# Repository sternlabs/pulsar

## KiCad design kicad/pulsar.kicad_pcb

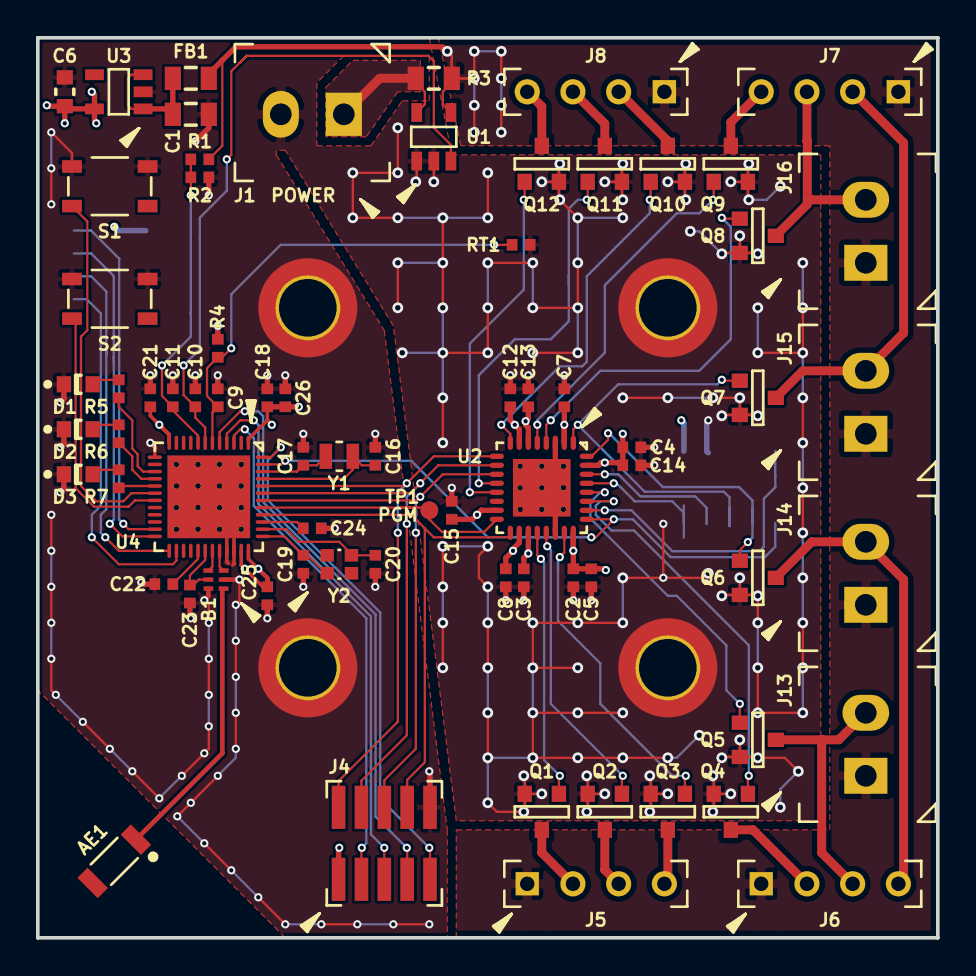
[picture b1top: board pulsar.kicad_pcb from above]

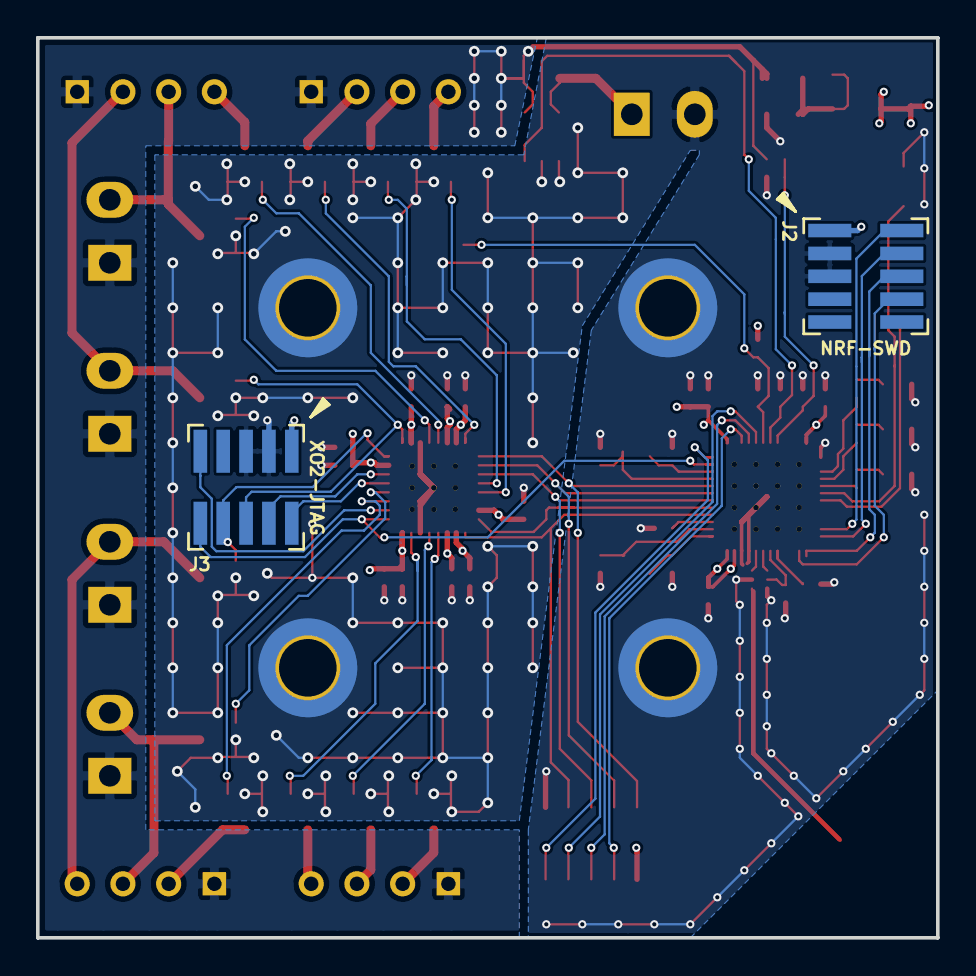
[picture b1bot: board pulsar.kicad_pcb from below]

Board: 4 copper layers, 50.0 x 50.0 mm, 77 parts (2 on the bottom side), 67 nets.

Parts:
AE1: ANT; ANT3216
B1: nRF-BALUN; BALUN-2450BM14E0003
C1: 10u; SMD-2012
C2, C3, C4, C7, C8, C12, C13, C14, C18, C21, C24: 100n; SMD-1005
C5, C15, C26: 1u; SMD-1005
C6: 4.7u; SMD-1608
C9, C10, C11, C22: 47n; SMD-1005
C16, C17: 20p; SMD-1005
C19, C20: 7p; SMD-1005
C23, C25: 2.2n; SMD-1005
D1, D2, D3: LED; SMD-1608-LED
FB1: FERRITE; SMD-2012
J1: POWER; TERM-2-3.5-PTH
J2: NRF-SWD; CONN-2x5-1.27-SMT
J3: XO2-JTAG; CONN-2x5-1.27-SMT
J4: CONN-2x5; CONN-2x5-1.27-SMT
J5, J6, J7, J8: CONN-4; CONN-4-2.54-0.8-PTH
J13, J14, J15, J16: CONN-2; TERM-2-3.5-PTH
MH1, MH2, MH3, MH4: MOUNTHOLE; HOLE-M3-COND
Q1, Q2, Q3, Q4, Q5, Q6, Q7, Q8, Q9, Q10, Q11, Q12: NMOS; SOT-23-FET
R1: 124k; SMD-1005
R2: 10k; SMD-1005
R3: 5m; SMD-2012
R4: 22k; SMD-1005
R5, R6, R7: 1k; SMD-1005
RT1: 47k; SMD-1005
S1, S2: TACTILE-4; TACT-4632
TP1: PGM; TESTPOINT-1.0
U1: TS1102-50; SOT-23-5
U2: XO2-256; xo2-256-qfn32
U3: MIC5205; SOT-23-5
U4: nrf51822; nrf51822-qfn48
Y1: 32kHz; OSC2012
Y2: 32MHz; OSC2016

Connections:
+3V3: C2.1, C3.1, C4.1, C5.1, C6.1, C7.1, C8.1, C12.1, C13.1, C14.1, C15.1, C18.1, C21.1, C25.1, C26.1, J2.1, J3.1, J4.1, R4.1, U2.2, U2.6, U2.7, U2.15, U2.18, U2.19, U2.24, U2.31, U3.5, U4.1, U4.12, U4.35, U4.36
/ANT: AE1.ANT, B1.1
/AUX1: J4.3, U4.3
/AUX2: J4.5, U4.4
/AUX3: J4.7, U4.5
/AUX4: J4.9, U4.48
/BUTTON1: S1.2, U4.18
/BUTTON2: S2.2, U4.19
/IIN_SENSE: C10.1, U1.3, U4.7
/LED1: R5.1, U4.15
/LED2: R6.1, U4.16
/LED3: R7.1, U4.17
/NRF_SWDCLK: J2.4, U4.24
/NRF_SWDIO/~RESET: J2.2, U4.23
/RAW_VIN: J1.1, R3.1, U1.5
/RX: J2.8, U4.26
/SPI_CLK: J4.2, U2.9, U4.44
/SPI_CS: J4.6, U2.11, U4.42
/SPI_CS_PGM: TP1.TP, U2.16, U4.41
/SPI_MISO: J4.4, U2.10, U4.43
/SPI_MOSI: J4.8, U2.17, U4.40
/TEMP_SENSE: C9.1, R4.2, RT1.1, U4.6
/TX: J2.6, U4.25
/VIN_SENSE: C11.1, R1.2, R2.1, U4.8
/XO2_JTAG_TCK: J3.4, U2.30
/XO2_JTAG_TMS: J3.2, U2.29
/rgb1/CH1: Q1.G, U2.20
/rgb1/CH1_OUT: J5.2, Q1.D
/rgb1/CH2: Q2.G, U2.21
/rgb1/CH2_OUT: J5.3, Q2.D
/rgb1/CH3: Q3.G, U2.23
/rgb1/CH3_OUT: J5.4, Q3.D
/rgb2/CH1: Q4.G, U2.27
/rgb2/CH1_OUT: J6.2, Q4.D
/rgb2/CH2: Q5.G, U2.28
/rgb2/CH2_OUT: J6.3, J13.2, Q5.D
/rgb2/CH3: J3.8, Q6.G, U2.32
/rgb2/CH3_OUT: J6.4, J14.2, Q6.D
/rgb3/CH1: J3.6, Q7.G, U2.1
/rgb3/CH1_OUT: J7.2, J15.2, Q7.D
/rgb3/CH2: Q8.G, U2.4
/rgb3/CH2_OUT: J7.3, J16.2, Q8.D
/rgb3/CH3: Q9.G, U2.5
/rgb3/CH3_OUT: J7.4, Q9.D
/rgb4/CH1: Q10.G, U2.8
/rgb4/CH1_OUT: J8.2, Q10.D
/rgb4/CH2: Q11.G, U2.12
/rgb4/CH2_OUT: J8.3, Q11.D
/rgb4/CH3: Q12.G, U2.13
/rgb4/CH3_OUT: J8.4, Q12.D
/~XO2_JTAG_EN: J3.9, U2.26
/~XO2_RESET: J3.10, U2.25, U4.47
unnamed: B1.3, U4.32
unnamed: B1.4, U4.31
unnamed: B1.5, C23.1, U4.30
unnamed: C1.1, FB1.2, U3.1, U3.3
unnamed: C16.1, U4.45, Y1.1
unnamed: C17.1, U4.46, Y1.2
unnamed: C19.1, U4.37, Y2.1
unnamed: C20.1, U4.38, Y2.3
unnamed: C22.1, U4.29
unnamed: C24.1, U4.39
unnamed: D1.A, R5.2
unnamed: D2.A, R6.2
unnamed: D3.A, R7.2
PGND: B1.2, B1.6, C1.2, C2.2, C3.2, C4.2, C5.2, C6.2, C7.2, C8.2, C9.2, C10.2, C11.2, C12.2, C13.2, C14.2, C15.2, C16.2, C17.2, C18.2, C19.2, C20.2, C21.2, C22.2, C23.2, C24.2, C25.2, C26.2, D1.C, D2.C, D3.C, J1.2, J2.3, J2.5, J3.3, J3.5, J4.10, MH1.1, MH2.1, MH3.1, MH4.1, Q1.S, Q2.S, Q3.S, Q4.S, Q5.S, Q6.S, Q7.S, Q8.S, Q9.S, Q10.S, Q11.S, Q12.S, R2.2, RT1.2, S1.3, S1.4, S2.3, S2.4, U1.1, U1.2, U2.3, U2.22, U2.FLAG, U3.2, U4.13, U4.33, U4.34, U4.FLAG
VIN: FB1.1, J5.1, J6.1, J7.1, J8.1, J13.1, J14.1, J15.1, J16.1, R1.1, R3.2, U1.4

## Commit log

2014-09-12 kicad blank project and libs
2014-09-12 update nrf51 lib, basic nrf schematic
2014-09-21 symbol rework
2014-10-04 update schematic
2014-10-05 R code to estimate NTC values for voltage divider
2014-10-05 add temp sense, rearrange schematic
2014-10-06 add headers
2014-10-06 fix connection
2014-10-07 add uart to swd connector
2014-10-09 add 32kHz crystal
2014-10-09 start assigning footprints
2014-10-13 start layout
2014-10-15 more layouting
2014-10-16 more layout
2014-10-16 antenna feed calculations
2014-10-17 layout progress
2014-10-22 layout
2014-10-28 switch to 4 layers
2014-10-30 layout work
2014-11-01 layout finish
2014-11-01 layout tweaks
2014-11-01 layout changes
2014-11-01 add small logo
2014-11-01 add Makefile
2015-05-19 update component values, bring out values on assembly layer
